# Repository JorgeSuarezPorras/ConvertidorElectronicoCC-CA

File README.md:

# Electronic Converter DC-AC
In this repository you will find all the files contained in the project: CURRENT CONTROL IN A DC-AC ELECTRONIC CONVERTER VIA MICROCONTROLLER.

It is recommended to read the detailed information of the project contained in the file: BachelorThesis.pdf

# Steps
The files are available in Matlab R2019a version.
## Steps to simulate the converter:
Once the folder is downloaded, you must:
1. Run: Software_Matlab.m
2. Open: Simulador_Simulink.slx
3. In the Simulador_Simulink.slx file, modify the mask with the necessary values and execute the program (RUN).

## Steps to run the programs in the converter:
Once the folder is downloaded, you must:
1. Run: Software_Matlab.m
2. Open: VSC_Simulink.slx
3. In the Simulator_Simulink.slx file, modify the mask with the necessary values and run the program (Deploy to Hardware)
4. It is important not to be feeding the microcontroller at 48V. If not, it would give an error.

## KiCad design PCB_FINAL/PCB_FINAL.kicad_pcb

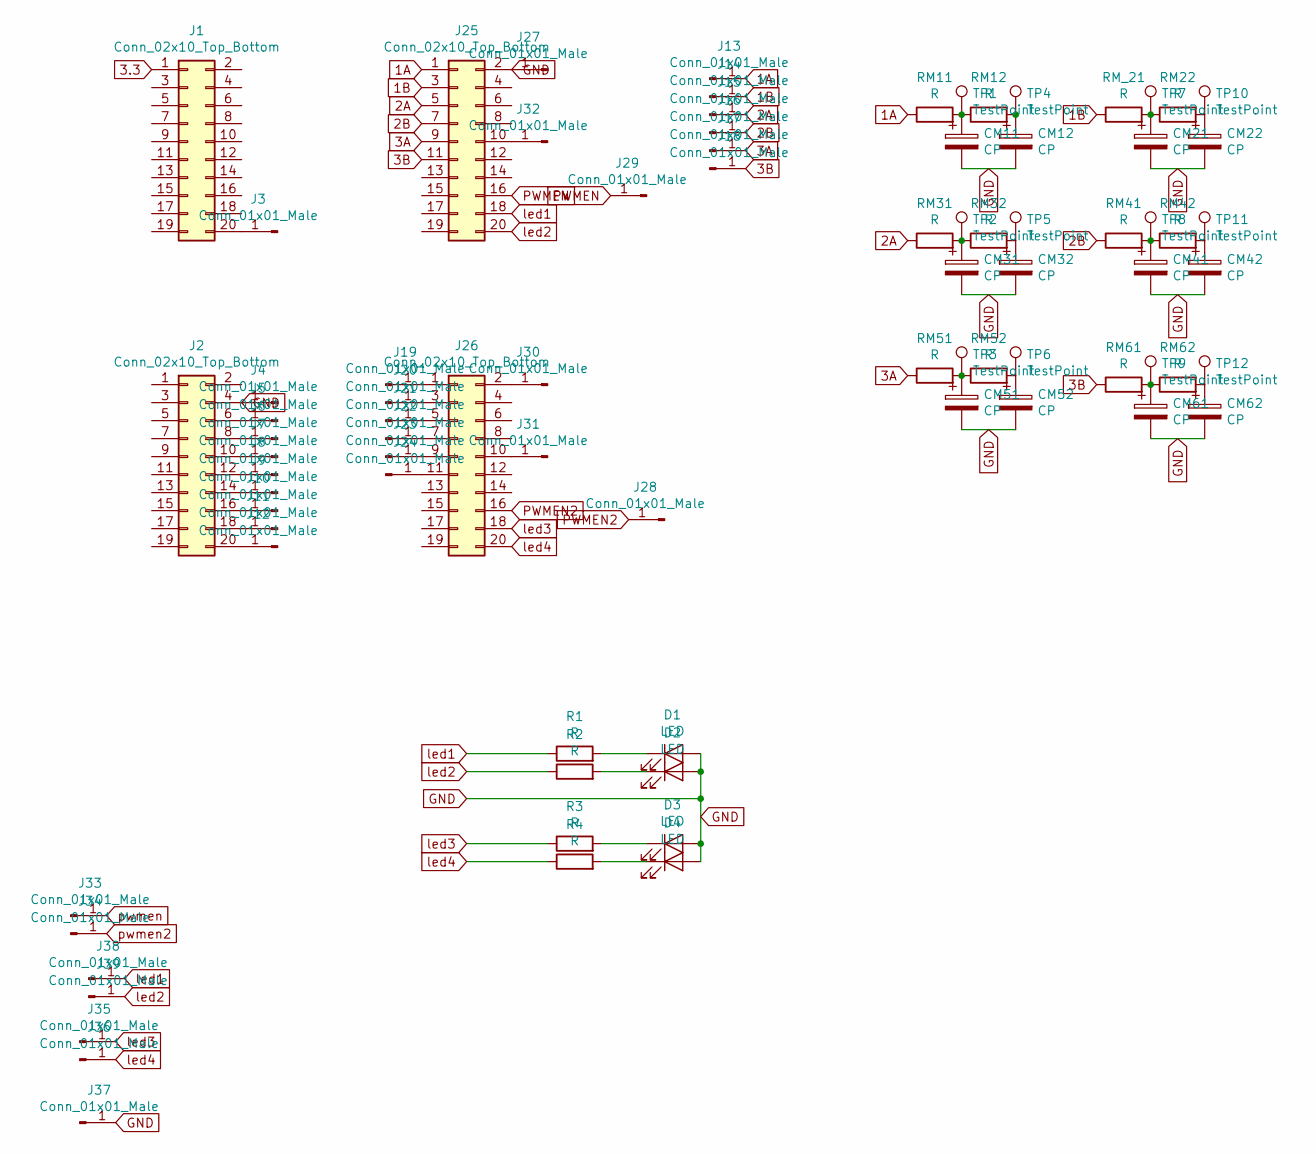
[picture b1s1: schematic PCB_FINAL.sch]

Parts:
CM11, CM12, CM21, CM22, CM31, CM32, CM41, CM42, CM51, CM52, CM61, CM62: CP; C_0805_2012Metric_Pad1.15x1.40mm_HandSolder
D1, D2, D3, D4: LED; LED_1206_3216Metric
J1, J2, J25, J26: Conn_02x10_Top_Bottom; PinHeader_2x10_P2.54mm_Vertical
J3, J4, J5, J6, J7, J8, J9, J10, J11, J12, J13, J14, J15, J16, J17, J18, J19, J20, J21, J22, J23, J24, J27, J28, J29, J30, J31, J32, J33, J34, J35, J36, J37, J38, J39: Conn_01x01_Male; TestPoint_Loop_D2.54mm_Drill1.5mm_Beaded
R1, R2, R3, R4: R; R_0805_2012Metric_Pad1.15x1.40mm_HandSolder
RM11, RM12, RM22, RM31, RM32, RM41, RM42, RM51, RM52, RM61, RM62: R; R_0805_2012Metric_Pad1.15x1.40mm_HandSolder
RM_21: R; R_0805_2012Metric_Pad1.15x1.40mm_HandSolder
TP1, TP2, TP3, TP4, TP5, TP6, TP7, TP8, TP9, TP10, TP11, TP12: TestPoint; BNC_TEConnectivity_1478204_Vertical

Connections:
1A: J13.1, J25.1, RM11.1
1B: J14.1, J25.3, RM_21.1
2A: J15.1, J25.5, RM31.1
2B: J16.1, J25.7, RM41.1
3.3: J1.1
3A: J17.1, J25.9, RM51.1
3B: J18.1, J25.11, RM61.1
GND: CM11.2, CM12.2, CM21.2, CM22.2, CM31.2, CM32.2, CM41.2, CM42.2, CM51.2, CM52.2, CM61.2, CM62.2, D1.2 (A), D2.2 (A), D3.2 (A), D4.2 (A), J2.4, J4.1, J25.2, J27.1, J37.1, TP1.2, TP2.2, TP3.2, TP4.2, TP5.2, TP6.2, TP7.2, TP8.2, TP9.2, TP10.2, TP11.2, TP12.2; also elsewhere on the board
unnamed: CM11.1, RM11.2, RM12.1, TP1.1
unnamed: CM12.1, RM12.2, TP4.1
unnamed: CM21.1, RM22.1, RM_21.2, TP7.1
unnamed: CM22.1, RM22.2, TP10.1
unnamed: CM31.1, RM31.2, RM32.1, TP2.1
unnamed: CM32.1, RM32.2, TP5.1
unnamed: CM41.1, RM41.2, RM42.1, TP8.1
unnamed: CM42.1, RM42.2, TP11.1
unnamed: CM51.1, RM51.2, RM52.1, TP3.1
unnamed: CM52.1, RM52.2, TP6.1
unnamed: CM61.1, RM61.2, RM62.1, TP9.1
unnamed: CM62.1, RM62.2, TP12.1
unnamed: D1.1 (K), R1.2
unnamed: D2.1 (K), R2.2
unnamed: D3.1 (K), R3.2
unnamed: D4.1 (K), R4.2
unnamed: J1.20, J3.1
unnamed: J2.6, J5.1
unnamed: J2.8, J6.1
unnamed: J2.10, J7.1
unnamed: J2.12, J8.1
unnamed: J2.14, J9.1
unnamed: J2.16, J10.1
unnamed: J2.18, J11.1
unnamed: J2.20, J12.1
unnamed: J19.1, J26.1
unnamed: J20.1, J26.3
unnamed: J21.1, J26.5
unnamed: J22.1, J26.7
unnamed: J23.1, J26.9
unnamed: J24.1, J26.11
unnamed: J25.10, J32.1
unnamed: J26.2, J30.1
unnamed: J26.10, J31.1
PWMEN: J25.16, J29.1
PWMEN2: J26.16, J28.1
led1: J25.18, J38.1, R1.1
led2: J25.20, J39.1, R2.1
led3: J26.18, J35.1, R3.1
led4: J26.20, J36.1, R4.1

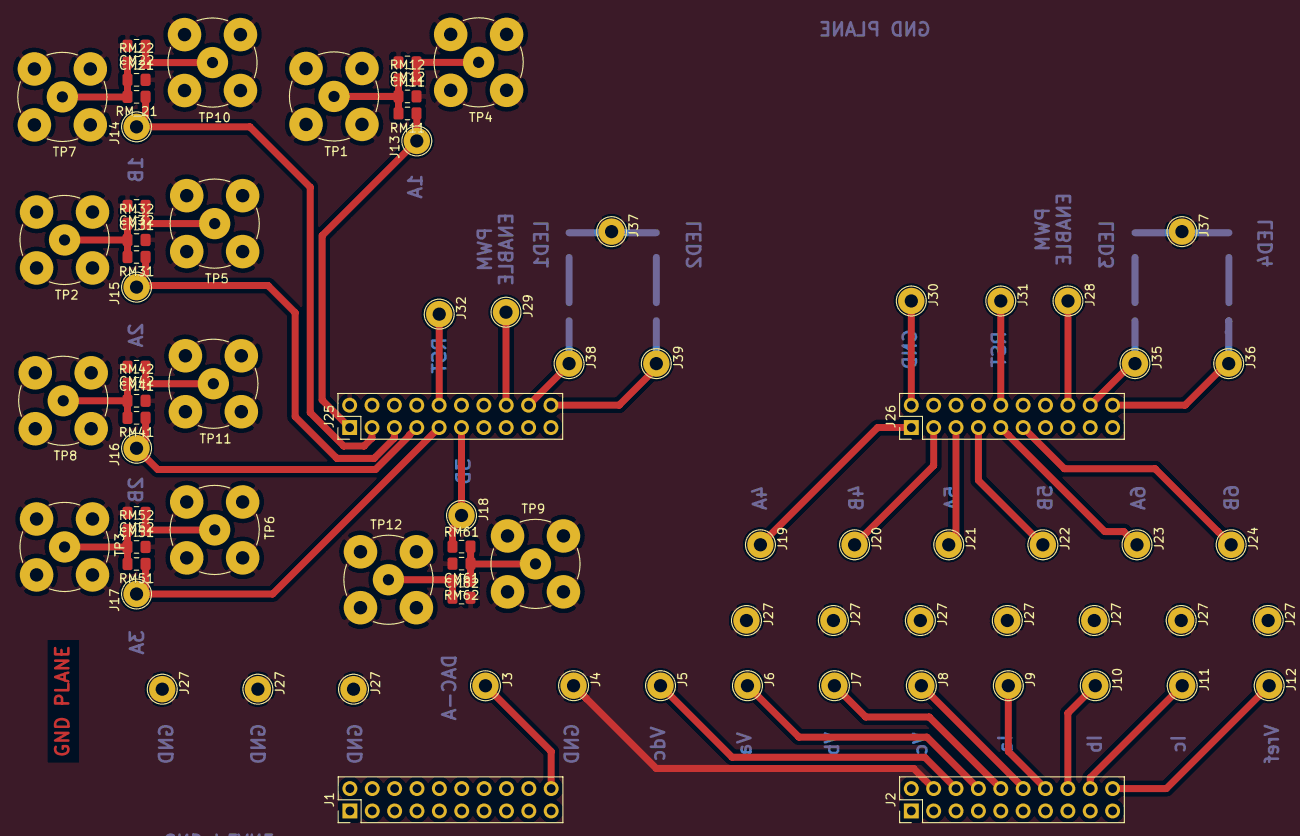
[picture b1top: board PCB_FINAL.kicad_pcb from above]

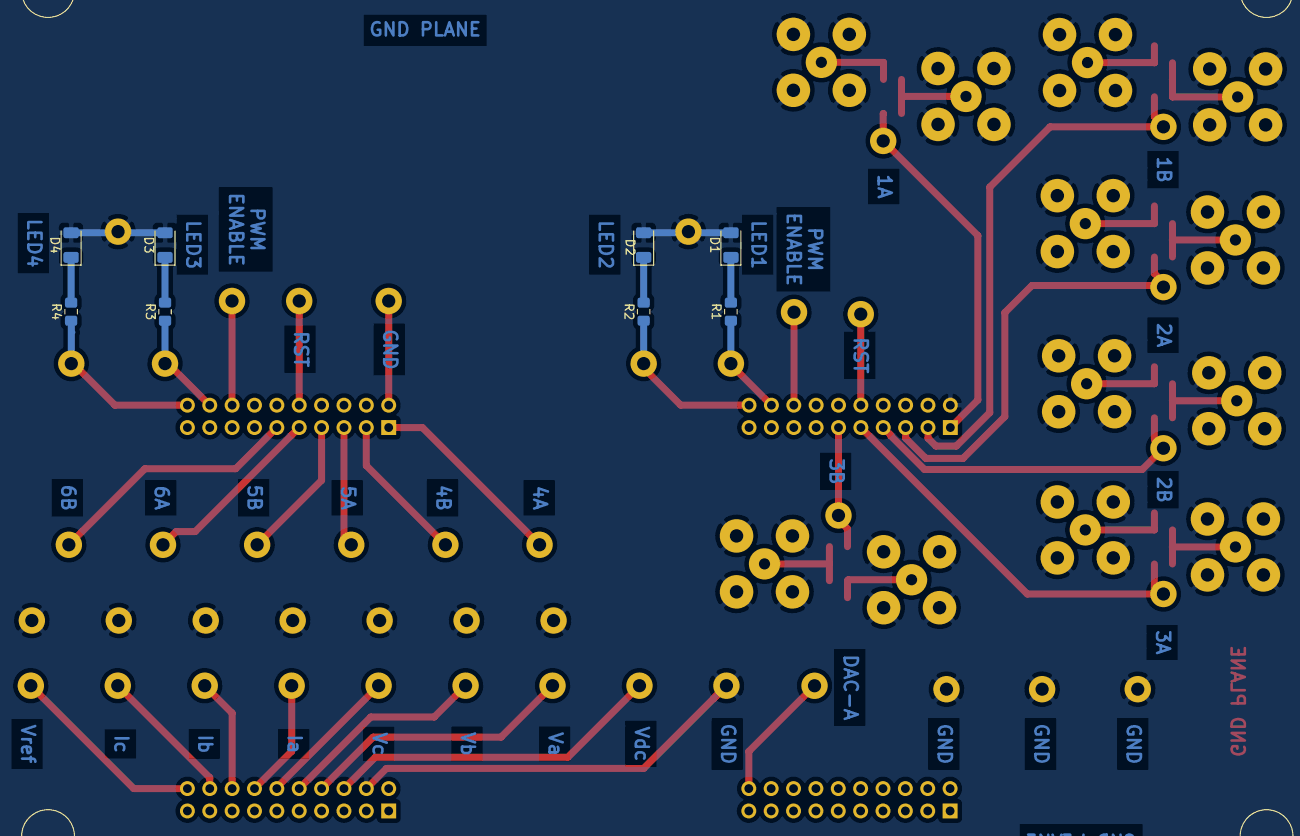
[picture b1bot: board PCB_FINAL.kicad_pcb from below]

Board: 2 copper layers, 91 parts (8 on the bottom side), 47 nets.

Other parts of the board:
J27#2, J27#3, J27#4, J27#5, J27#6, J27#7, J27#8, J27#9, J27#10, J37#2: Conn_01x01_Male; TestPoint_Loop_D2.54mm_Drill1.5mm_Beaded

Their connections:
GND: J27#2.1, J27#3.1, J27#4.1, J27#5.1, J27#6.1, J27#7.1, J27#8.1, J27#9.1, J27#10.1, J37#2.1; also elsewhere on the board

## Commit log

2020-02-06 Add files via upload
    Documento Trabajo fin de grado: Control de Corriente en un Convertidor CC- CA mediante Microcontrolador.
2020-05-19 Click.png interfaz
2020-05-19 2019b version y click.png
2020-05-20 Fixed some errors
2020-06-11 Added and changed LED configurations
2020-06-26 Protocolo de Prácticas
2020-07-17 PCB Board for measurements
    Kicad board
2020-07-25 Added PCB design
2020-09-26 Corrected errors related to open-loop simulator
    Decoupling of the inductances when working in open-loop.
2020-12-16 Bachelor Thesis in English
2021-08-21 Protocolo de Prácticas
    Protocolo de prácticas para seguir en el laboratorio
2022-08-02 Bachelor's Thesis in English
